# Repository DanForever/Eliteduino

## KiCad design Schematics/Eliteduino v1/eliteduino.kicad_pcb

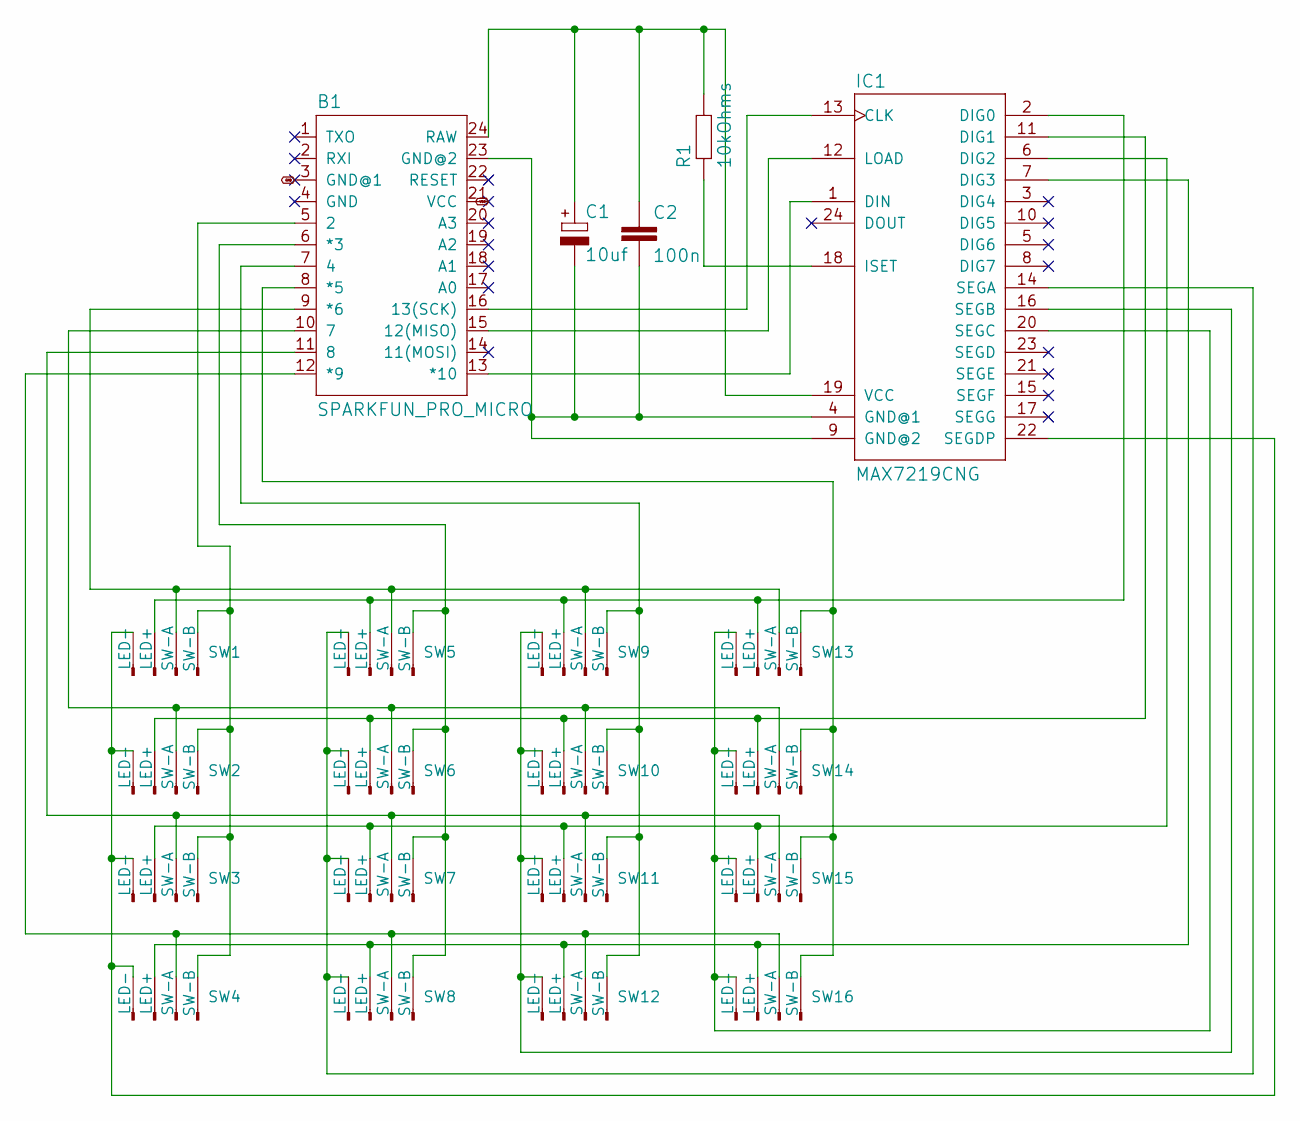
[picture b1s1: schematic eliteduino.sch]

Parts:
B1: SPARKFUN_PRO_MICRO
C1: 10uf; E2-5
C2: 100n; C025-024X044
IC1: MAX7219CNG; DIL24-3
R1: 10kOhms; 0204_7
SW1, SW2, SW3, SW4, SW5, SW6, SW7, SW8, SW9, SW10, SW11, SW12, SW13, SW14, SW15, SW16: SW_Connector; JST_EH_B4B-EH-A_1x04_P2.50mm_Vertical

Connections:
GND: B1.3 (GND@1)
unnamed: B1.5 (2), SW1.4 (SW-B), SW2.4 (SW-B), SW3.4 (SW-B), SW4.4 (SW-B)
unnamed: B1.6 (*3), SW5.4 (SW-B), SW6.4 (SW-B), SW7.4 (SW-B), SW8.4 (SW-B)
unnamed: B1.7 (4), SW9.4 (SW-B), SW10.4 (SW-B), SW11.4 (SW-B), SW12.4 (SW-B)
unnamed: B1.8 (*5), SW13.4 (SW-B), SW14.4 (SW-B), SW15.4 (SW-B), SW16.4 (SW-B)
unnamed: B1.9 (*6), SW1.3 (SW-A), SW5.3 (SW-A), SW9.3 (SW-A), SW13.3 (SW-A)
unnamed: B1.10 (7), SW2.3 (SW-A), SW6.3 (SW-A), SW10.3 (SW-A), SW14.3 (SW-A)
unnamed: B1.11 (8), SW3.3 (SW-A), SW7.3 (SW-A), SW11.3 (SW-A), SW15.3 (SW-A)
unnamed: B1.12 (*9), SW4.3 (SW-A), SW8.3 (SW-A), SW12.3 (SW-A), SW16.3 (SW-A)
unnamed: B1.13 (*10), IC1.1 (DIN)
unnamed: B1.15 (12(MISO)), IC1.12 (LOAD)
unnamed: B1.16 (13(SCK)), IC1.13 (CLK)
unnamed: B1.23 (GND@2), C1.-, C2.2, IC1.4 (GND@1), IC1.9 (GND@2)
unnamed: B1.24 (RAW), C1.+, C2.1, IC1.19 (VCC), R1.2
unnamed: IC1.2 (DIG0), SW1.2 (LED+), SW5.2 (LED+), SW9.2 (LED+), SW13.2 (LED+)
unnamed: IC1.6 (DIG2), SW3.2 (LED+), SW7.2 (LED+), SW11.2 (LED+), SW15.2 (LED+)
unnamed: IC1.7 (DIG3), SW4.2 (LED+), SW8.2 (LED+), SW12.2 (LED+), SW16.2 (LED+)
unnamed: IC1.11 (DIG1), SW2.2 (LED+), SW6.2 (LED+), SW10.2 (LED+), SW14.2 (LED+)
unnamed: IC1.14 (SEGA), SW5.1 (LED-), SW6.1 (LED-), SW7.1 (LED-), SW8.1 (LED-)
unnamed: IC1.16 (SEGB), SW9.1 (LED-), SW10.1 (LED-), SW11.1 (LED-), SW12.1 (LED-)
unnamed: IC1.18 (ISET), R1.1
unnamed: IC1.20 (SEGC), SW13.1 (LED-), SW14.1 (LED-), SW15.1 (LED-), SW16.1 (LED-)
unnamed: IC1.22 (SEGDP), SW1.1 (LED-), SW2.1 (LED-), SW3.1 (LED-), SW4.1 (LED-)
VCC: B1.21 (VCC)

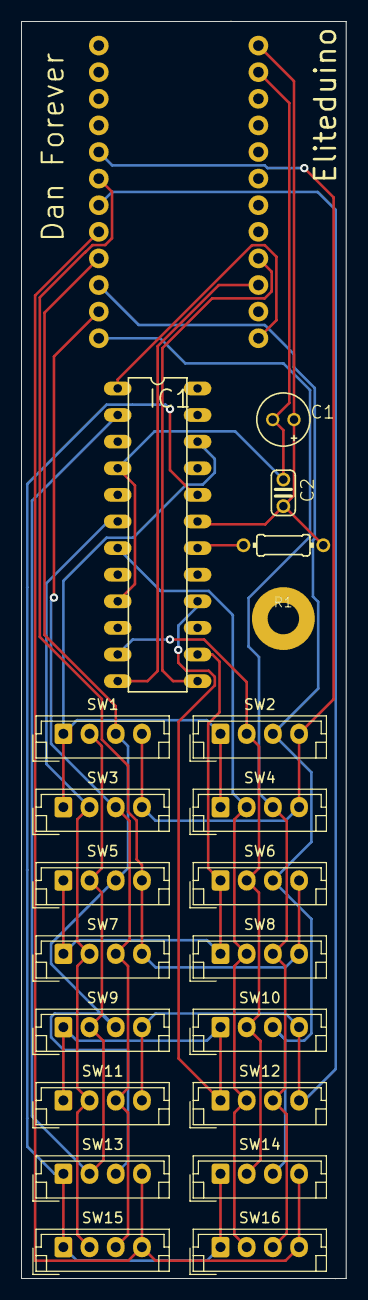
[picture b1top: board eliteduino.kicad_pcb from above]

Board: 2 copper layers, 31.0 x 120.0 mm, 21 parts (0 on the bottom side), 22 nets.

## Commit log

2020-12-29 Added PyHid as a dependency (submodule)
2020-12-29 "hello world" load.py
    This is a basic load.py with enough logic to trigger an LED on the prototype as a test
2020-12-29 install utility
    Will install everything we need to ensure the latest plugin is installed into the EDMC plugins folder
2021-02-07 First commit of the control panel firmware
    Features:
    * Displays player name, current system, and location within system with icons
    * No support for button controls yet
    So far only tested with a Teensy 4.0 with ILI9341 screen module
2021-02-08 Custom replacements for the standard teensy library
    These are intended to be placed over the top of the teensy install during a build
2021-02-09 Custom boards.txt required to enable our custom RawHid + keyboard config
2021-02-09 Initial version of Travis-CI integration scripts
2021-02-09 Added travis-ci build status
2021-02-09 Moved Travis CI configuration file into repository root
2021-02-11 Project restructuring to allow for modular builds
    The idea here is to allow for different builds to target different devices. One may have a screen, another only buttons.
    Also will allow for different micro-controllers (not just Teensyduino)
    The bulk of the code so far has been moved into the "display module", the HID communication part needs to be broken out and made more generic still
2021-02-12 Refactored hid communication out of screen layer into more generic location that can be used for multiple systems
2021-02-13 Refactored Event to no longer use lambdas as std::function is not supported by standard arduino (and other compatibility changes)
2021-02-14 Refactoring of PC communications (HID) done
    Still works for teensy, in theory it also works for pro micro, but we still need to test it
2021-02-17 Initial version of button matrix implementation
    A button matrix is defined and polled according to the current design of the pro micro Eliteduino
    Still todo:
    - Activate callbacks on button press and release
    - Defining button-press to PC input binding
    - Communication with PC to allow for rebinding
2021-02-17 Added "Bounce2" library dependency to the travis-ci script
2021-02-18 Any button press/release now sends a hardcoded gamepad button 2 press/release to the PC
2021-02-19 Compile fix for teensy build configuration
2021-02-19 Disable device configurations by default so that they can be enabled by CI
2021-02-19 Potential update to travis-ci yaml configuration so that both teensy and pro micro variants are built
    For Teensy, due to the limitations of how the build system integration has to be configured, in order to apply custom pre-processor macros at build time, we need to hard code the compiler arguments i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
    We could workaround this by effectively creating a new fake board that is a copy of teensy40, but it's not the best solution.
    The Pro micro uses arduino-cli, which in theory, should "just work"
2021-02-20 Added missing boards dependency for pro micro build
2021-02-20 Attempting travis-ci fix
    Error is:
    0.29s$ $HOME/arduino_ide/arduino-cli core --additional-urls $SPARKFUN_BOARDS_URL install SparkFun:avr
    Error installing: error loading platform index:
    loading json index file /home/travis/.arduino15/package_sparkfun_index.json: open /home/travis/.arduino15/package_sparkfun_index.json: no such file or directory
    The command "$HOME/arduino_ide/arduino-cli core --additional-urls $SPARKFUN_BOARDS_URL install SparkFun:avr" failed and exited with 1 during .
2021-02-20 Added missing "ArxContainer" library to the travis-ci yaml
2021-02-20 An attempt to fix *the next* travis-ci build error
    Error:
    $HOME/arduino_ide/arduino-cli compile -b SparkFun:avr:promicro:cpu=8MHzatmega32U4 --build-property compiler.cpp.extra_flags=-D$DEVICE_CONFIG ControlPanel/ControlPanel.ino
    <command-line>:0:1: error: macro names must be identifiers
    Error during build: exit status 1
    The command "$HOME/arduino_ide/arduino-cli compile -b SparkFun:avr:promicro:cpu=8MHzatmega32U4 --build-property compiler.cpp.extra_flags=-D$DEVICE_CONFIG ControlPanel/ControlPanel.ino" exited with 1.
2021-02-20 Next attempt at fixing travis-ci build error for pro micro
2021-02-21 Button bindings
    Buttons now have bindings, these bindings are loaded and saved in the eeprom.
    On startup, the micro controller will check to see if there are valid bindings stored on the eeprom by checking a CRC.
    If there isn't a valid CRC, then a default configuration is saved onto the eeprom.
    Also added a debug print library to make printing to the console easier than using Serial.print
2021-02-21 Refactored usage of Serial.Print() into PRINT()
    Also disabled waiting for serial listener by default
2021-02-22 Kicad project for the Arduino pro micro Eliteduino
2021-03-14 Added support for current player status
    Adds information regarding things like "mass lock"
    Some refactoring to clean up how the data is updated
2021-03-14 Some refactoring to enable control of the LEDs
    There is now an LED "matrix" class, which is meant to be a companion to the Button "matrix". There is also an LED controller, which will allow for LEDs not controlled by a MAX chip/matrix.
    A similar refactor will need to happen to buttons so we have a "button controller" in addition to the matrix
2021-03-21 Refactored to fix compilation on Teensy
2021-04-03 Compiler warning fix
2021-04-04 The panel can now receive messages from EDMC that can control the LEDs
    Teensy devices can:
    - now send keyboard events
    Arduino (currently only the pro micro) devices can:
    - receive messages from the PC via Serial
2021-04-04 EDMC plugin can now use both HID and Serial to communicate with the control panel
    Serial communication uses pyserial, which has been added as a submodule of the project
2021-04-04 Fixed devices.h defines in repository
    The devices shouldn't be explicitly defined in the codebase itself (it's a failing of the arduino ide that they need to be enabled via code rather than compiler settings)
2021-04-05 Added LedControl to travis CI configuration
2021-04-05 Compile fixes for travis-ci
    - Disabled debug print by default
    - Removed calls to local debug code in hid library
    - hack to auto configure bindings wrapped in define
2021-04-05 The check for the overheating status value was testing against the wrong flag
2021-04-05 Blinking LED animation
    There is now an animation that alternates an LED every 250ms
    Animations have been added for the following controls:
    - Galaxy Map
    - System Map
    - Overheating
    - FSD Cooldown
2021-04-08 Cleaned up the debug options
2021-04-12 Fixed exceptions in debug_write_journal_entry_to_log
    Caused by incorrect assumptions about lifetimes of global variables
2021-04-12 Multi-device connections
    Also serial device disconnections are dealt with gracefully
    Some log spam cleanup
